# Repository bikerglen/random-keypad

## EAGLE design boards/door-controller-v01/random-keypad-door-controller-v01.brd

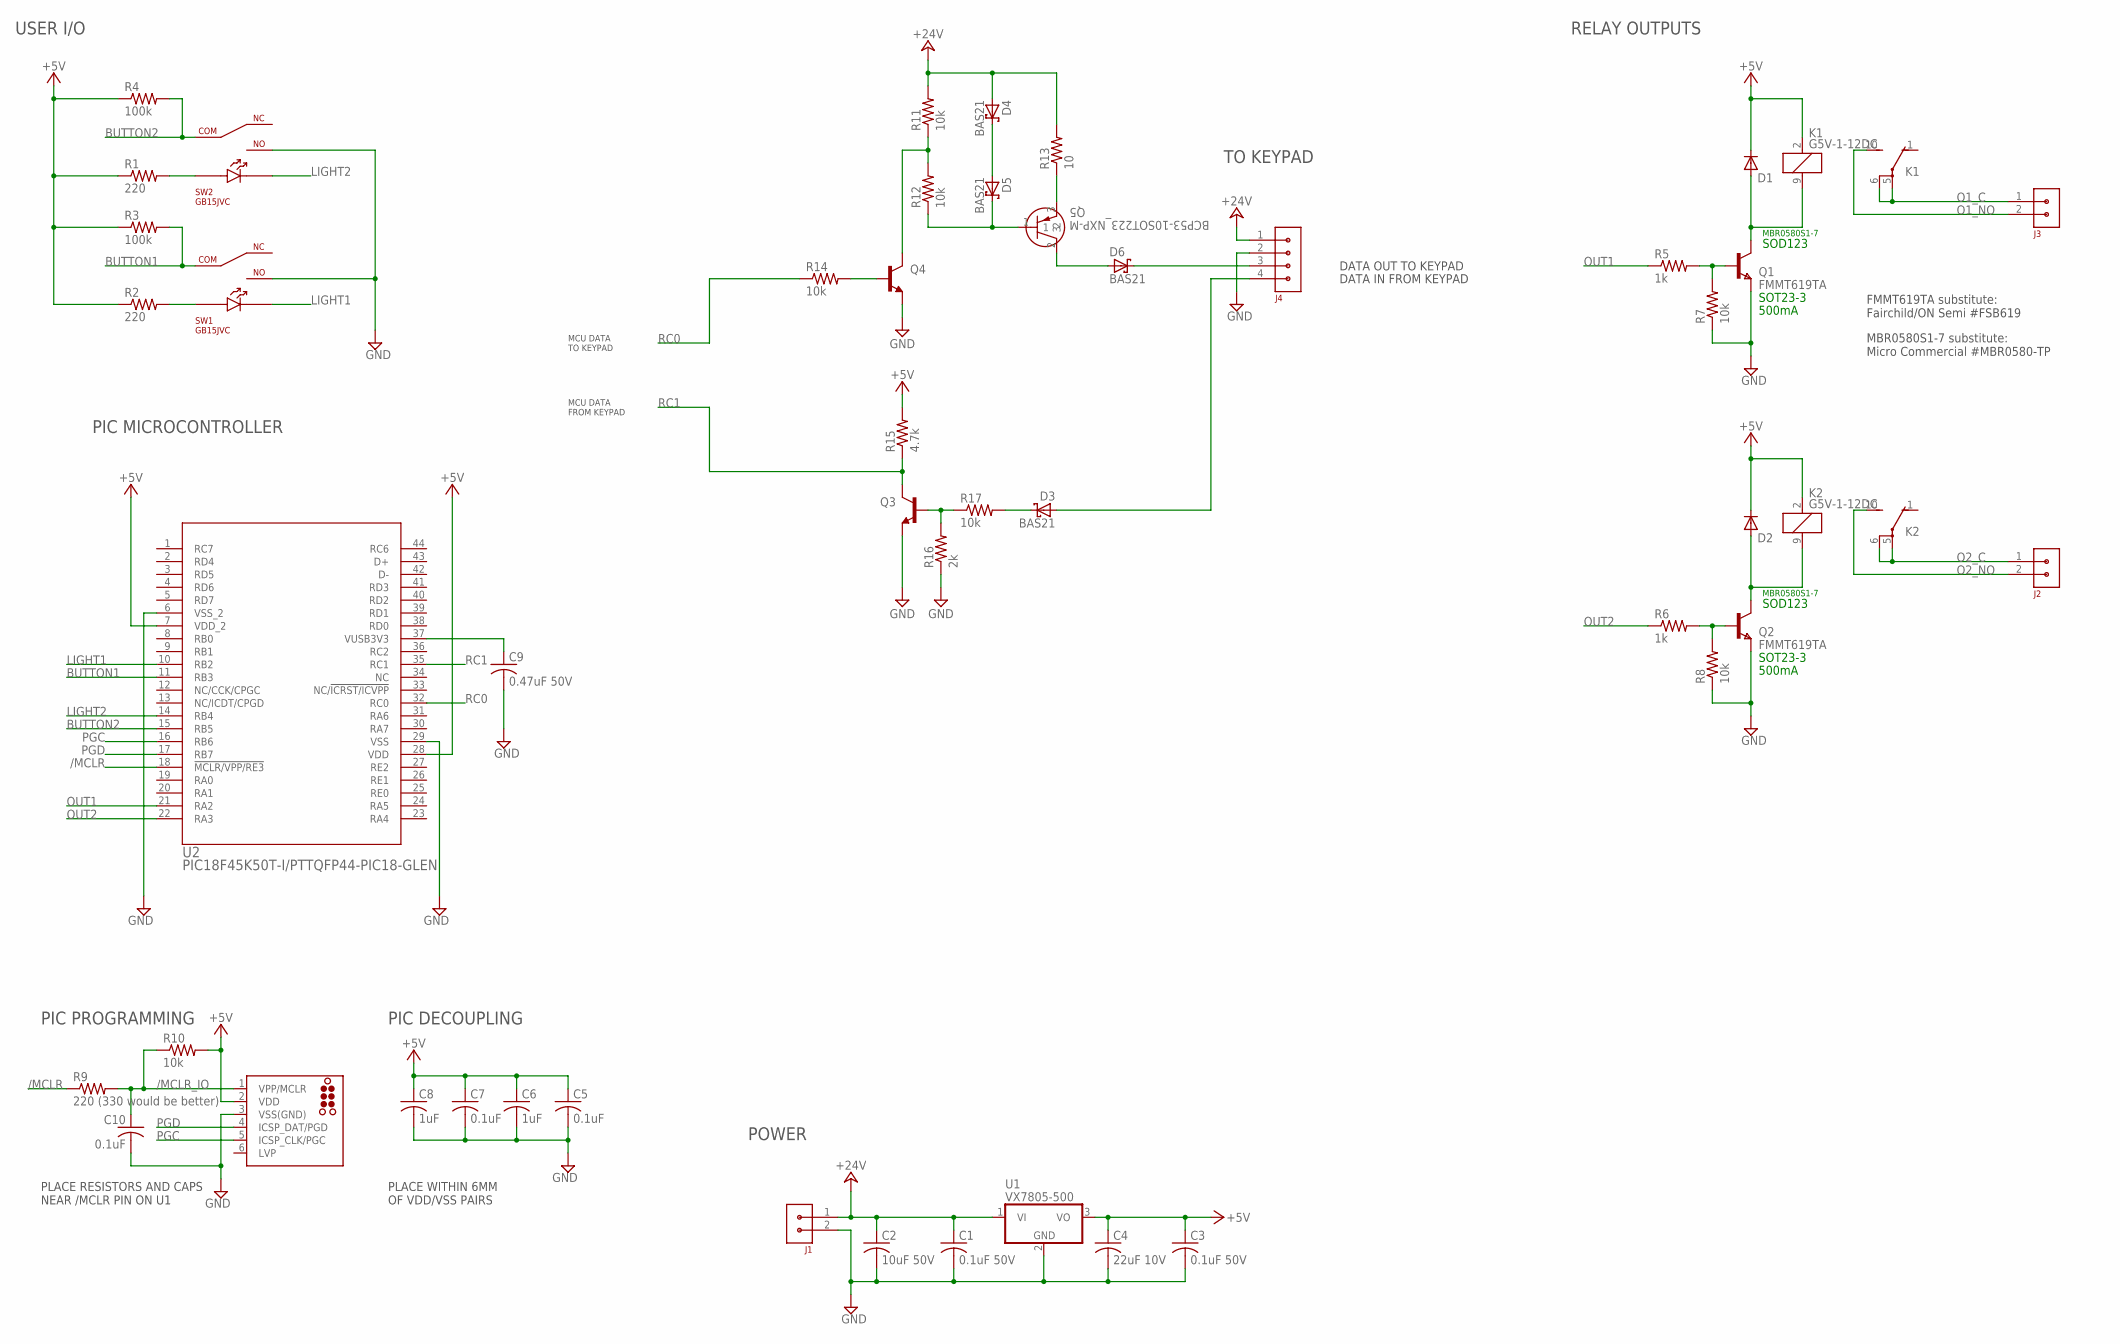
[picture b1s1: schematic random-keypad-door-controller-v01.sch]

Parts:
C1, C3: 0.1uF 50V; C1206K; MFR_PART_NO C1206S104M5RACTU
C2: 10uF 50V; C1210K; MFR_PART_NO C1210C106K5RACTU
C4: 22uF 10V; C1206K; MFR_PART_NO C1206C226K8RAC7800
C5, C7, C10: 0.1uF; C0603K
C6, C8: 1uF; C0603K
C9: 0.47uF 50V; C1206K; MFR_PART_NO C1206C474K5RACTU
D1, D2: 1N4148W-TP; SOD123; MFR_PART_NO MBR0580S1-7
D3, D4, D5, D6: BAS21; SOT23
DEBUG: TC2030-MCP-NL
J1, J2, J3: CON-3.81MM-1X2-PHOENIX; CON-PHOENIX-3.81-1X2-RA
J4: CON-3.81MM-1X4-PHOENIX-1803293; CON-PHOENIX-1803293-3.81-1X4
K1, K2: G5V-1-12DC; G5V1; MFR_PART_NO G5V-1-DC5
Q1, Q2: FMMT619TA; SOT-23; MFR_PART_NO FMMT619TA
Q3, Q4: BC817-40-NPN-SOT23-BEC; SOT23-BEC
Q5: BCP53-10SOT223_NXP-M; SOT223_NXP-M
R1, R2: 220; R0603
R3, R4: 100k; R0603
R5, R6: 1k; R0603; MFR_PART_NO CR1206-JW-102ELF
R7, R8: 10k; R0603; MFR_PART_NO CR1206-JW-102ELF
R9: 220 (330 would be better); R0603
R10, R11, R12, R14, R17: 10k; R0603
R13: 10; R0603
R15: 4.7k; R0603
R16: 2k; R0603
SW1, SW2: GB15JVC; GB15JHC
U1: VX7805-500; CUI-78XX-500
U2: PIC18F45K50T-I/PTTQFP44-PIC18-GLEN; TQFP44-PIC18-GLEN

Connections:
+5V: C3.1, C4.1, C5.1, C6.1, C7.1, C8.1, D1.C, D2.C, DEBUG.2 (VDD), K1.2 (1), K2.2 (1), R1.1, R2.1, R3.1, R4.1, R10.2, R15.2, U1.3 (VO), U2.7 (VDD_2), U2.28 (VDD)
+24V: C1.1, C2.1, D4.1 (A), J1.1, J4.1, R11.2, R13.2, U1.1 (VI)
/MCLR: R9.1, U2.18 (!MCLR/VPP/RE3)
/MCLR_IO: C10.1, DEBUG.1 (VPP/MCLR), R9.2, R10.1
BUTTON1: R3.2, SW1.5, U2.11 (RB3)
BUTTON2: R4.2, SW2.5, U2.15 (RB5)
GND: C1.2, C2.2, C3.2, C4.2, C5.2, C6.2, C7.2, C8.2, C9.2, C10.2, DEBUG.3 (VSS(GND)), J1.2, J4.2, Q1.2 (E), Q2.2 (E), Q3.E, Q4.E, R7.1, R8.1, R16.1, SW1.4, SW2.4, U1.2 (GND), U2.6 (VSS_2), U2.29 (VSS)
LIGHT1: SW1.3, U2.10 (RB2)
LIGHT2: SW2.3, U2.14 (RB4)
unnamed: Q2.3 (B), R6.2, R8.2
unnamed: D2.A, K2.9 (2), Q2.1 (C)
unnamed: R1.2, SW2.1
unnamed: D6.1 (A), Q5.2
unnamed: R2.2, SW1.1
unnamed: D6.3 (C), J4.3
unnamed: D4.3 (C), D5.1 (A)
unnamed: Q5.3, R13.1
unnamed: Q4.C, R11.1, R12.2
unnamed: D5.3 (C), Q5.1, R12.1
unnamed: Q4.B, R14.2
unnamed: Q1.3 (B), R5.2, R7.2
unnamed: Q3.B, R16.2, R17.1
unnamed: D3.3 (C), R17.2
unnamed: D3.1 (A), J4.4
unnamed: D1.A, K1.9 (2), Q1.1 (C)
O1_C: J3.1, K1.5, K1.6
O1_NO: J3.2, K1.10 (S)
O2_C: J2.1, K2.5, K2.6
O2_NO: J2.2, K2.10 (S)
OUT1: R5.1, U2.21 (RA2)
OUT2: R6.1, U2.22 (RA3)
PGC: DEBUG.5 (ICSP_CLK/PGC), U2.16 (RB6)
PGD: DEBUG.4 (ICSP_DAT/PGD), U2.17 (RB7)
RC0: R14.1, U2.32 (RC0)
RC1: Q3.C, R15.1, U2.35 (RC1)
VUSB: C9.1, U2.37 (VUSB3V3)

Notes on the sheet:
USER I/O
SOD123
SOT23-3
500mA
MBR0580S1-7
FMMT619TA substitute: Fairchild/ON Semi #FSB619
MBR0580S1-7 substitute: Micro Commercial #MBR0580-TP
POWER
RELAY OUTPUTS
PIC DECOUPLING
PIC PROGRAMMING
PLACE WITHIN 6MM OF VDD/VSS PAIRS
PLACE RESISTORS AND CAPS NEAR /MCLR PIN ON U1
PIC MICROCONTROLLER
DATA OUT TO KEYPAD
DATA IN FROM KEYPAD
MCU DATA FROM KEYPAD
MCU DATA TO KEYPAD
TO KEYPAD

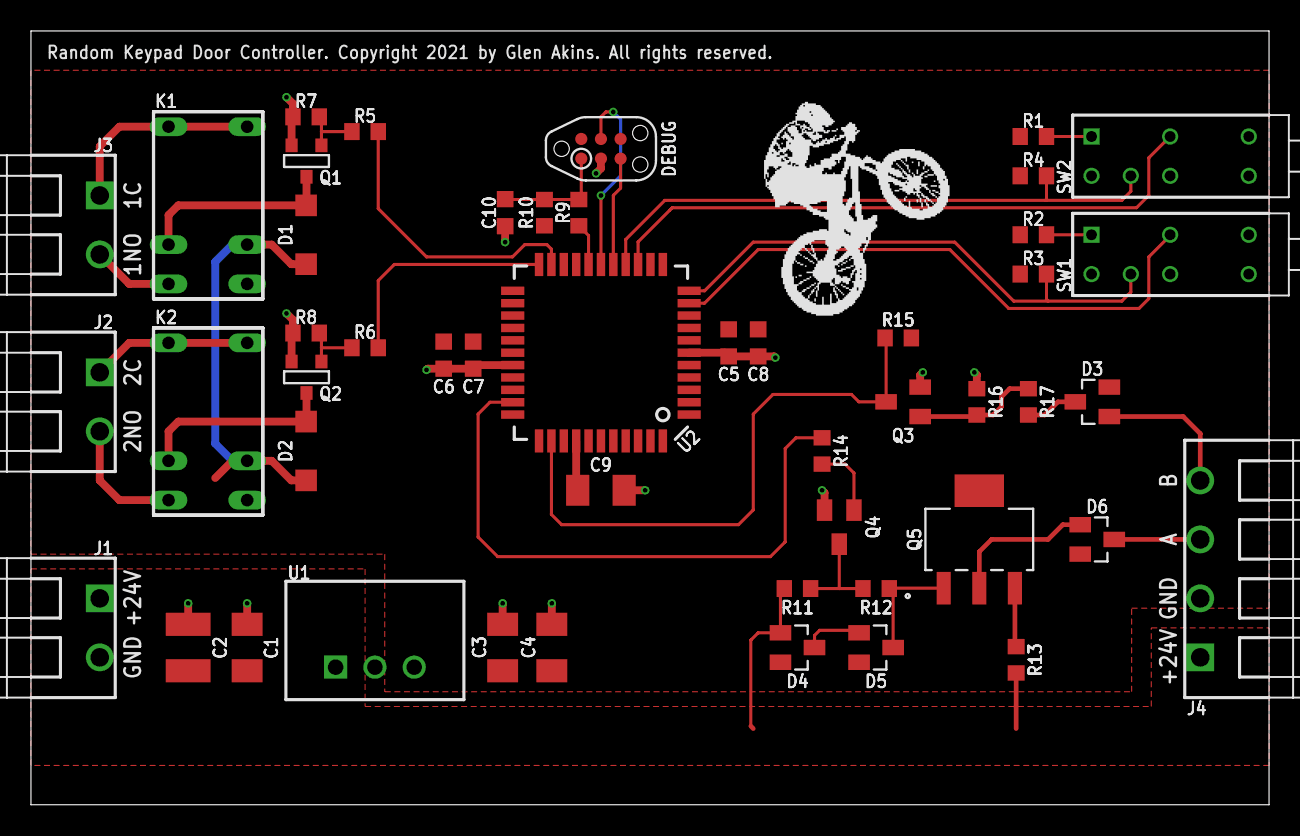
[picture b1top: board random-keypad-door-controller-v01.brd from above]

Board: 2 copper layers, 80.0 x 50.0 mm, 49 parts (0 on the bottom side), 36 nets.

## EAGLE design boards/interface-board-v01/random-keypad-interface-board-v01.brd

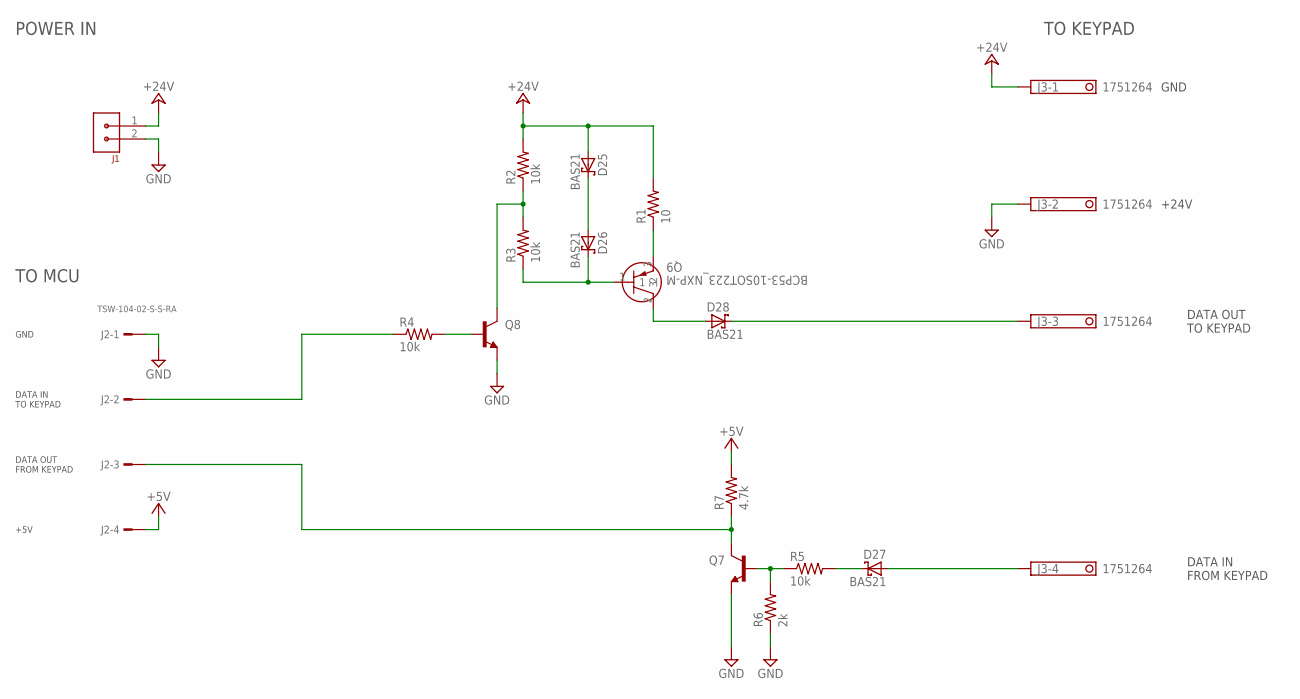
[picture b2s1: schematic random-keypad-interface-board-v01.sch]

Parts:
D25, D26, D27, D28: BAS21; SOT23
J1: CON-3.81MM-1X2-PHOENIX; CON-PHOENIX-3.81-1X2-RA
J2: TSW-104-02-S-S-RA
J3: 1751264
Q7, Q8: BC817-40-NPN-SOT23-BEC; SOT23-BEC
Q9: BCP53-10SOT223_NXP-M; SOT223_NXP-M
R1: 10; R0603
R2, R3, R4, R5: 10k; R0603
R6: 2k; R0603
R7: 4.7k; R0603

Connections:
+5V: J2.4, R7.2
+24V: D25.1 (A), J1.1, J3.1, R1.2, R2.2
GND: J1.2, J2.1, J3.2, Q7.E, Q8.E, R6.1
unnamed: D28.1 (A), Q9.2
unnamed: D28.3 (C), J3.3
unnamed: Q8.B, R4.2
unnamed: D25.3 (C), D26.1 (A)
unnamed: D26.3 (C), Q9.1, R3.1
unnamed: Q9.3, R1.1
unnamed: Q8.C, R2.1, R3.2
unnamed: Q7.B, R5.1, R6.2
unnamed: J2.2, R4.1
unnamed: D27.3 (C), R5.2
unnamed: D27.1 (A), J3.4
unnamed: J2.3, Q7.C, R7.1

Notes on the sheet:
GND
+24V
DATA OUT TO KEYPAD
DATA IN FROM KEYPAD
POWER IN
+5V
DATA OUT FROM KEYPAD
DATA IN TO KEYPAD
TO MCU
TO KEYPAD

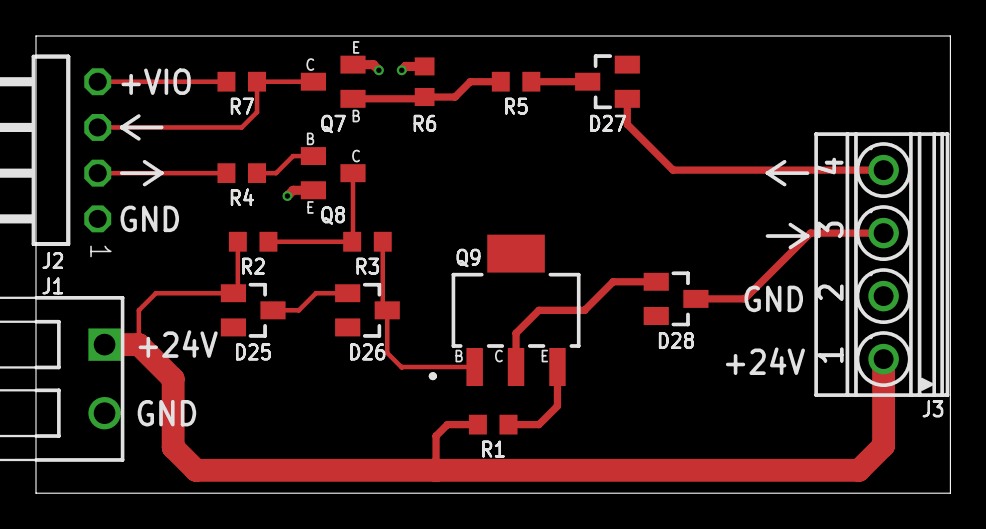
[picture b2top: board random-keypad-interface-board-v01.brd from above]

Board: 2 copper layers, 50.8 x 25.4 mm, 17 parts (0 on the bottom side), 15 nets.

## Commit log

2023-06-20 initial checkin

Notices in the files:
boards/door-controller-v01/random-keypad-door-controller-v01.brd:
Random Keypad Door Controller. Copyright 2021 by Glen Akins. All rights reserved.
parts and their libraries:
tag-connect: ©2009 ROFA.cz - modified and updated by Robert Darlington ‹rdarlington@gmail.com›
COPYRIGHT: Copyright (C) 2021 Ultra Librarian. All rights reserved.
PIC18F45K50: COPYRIGHT: Copyright (C) 2018 Accelerated Designs. All rights reserved
